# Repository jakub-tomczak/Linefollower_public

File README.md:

# Linefollower
Project created to compete with other linefollowers at PUT.

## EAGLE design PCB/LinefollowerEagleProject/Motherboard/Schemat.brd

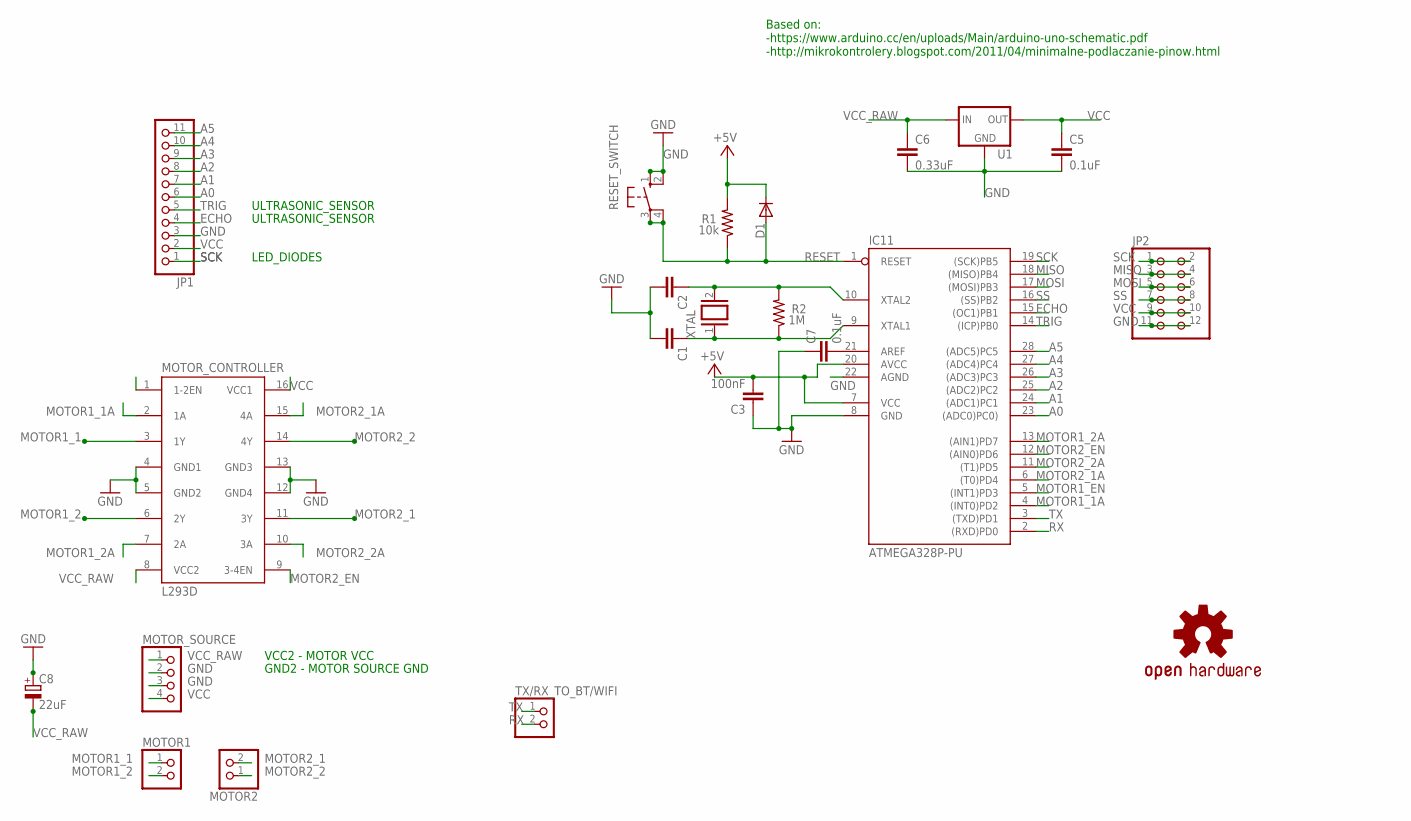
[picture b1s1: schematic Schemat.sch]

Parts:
C1, C2: C-EU025-030X050; C025-030X050
C3: 100nF; C025-030X050
C5: 0.1uF; CAP-PTH-SMALL-KIT
C6: 0.33uF; CAP-PTH-SMALL-KIT
C7: 0.1uF; C025-030X050
C8: 22uF; E2,5-6E
D1: 1N4004; DO41-10
IC11: ATMEGA328P-PU; DIL28-3
JP1: PINHD-1X11; 1X11
JP2: PINHD-2X6; 2X06
LOGO1: OSHW-LOGOS-COPPER; OSHW-LOGO-S_COPPER
MOTOR1, MOTOR2: PINHD-1X2/90; 1X02/90
MOTOR_CONTROLLER: L293D; DIL16
MOTOR_SOURCE: PINHD-1X4; 1X04
R1: 10k; AXIAL-0.3
R2: 1M; AXIAL-0.3
RESET_SWITCH: 10-XX; B3F-10XX
TX/RX_TO_BT/WIFI: PINHD-1X2/90; 1X02/90
U1: V_REG_78XX-TO-220; TO-220-ALT
XTAL: XTAL/S; QS

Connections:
A0: IC11.23 ((ADC0)PC0)), JP1.6
A1: IC11.24 ((ADC1)PC1), JP1.7
A2: IC11.25 ((ADC2)PC2), JP1.8
A3: IC11.26 ((ADC3)PC3), JP1.9
A4: IC11.27 ((ADC4)PC4), JP1.10
A5: IC11.28 ((ADC5)PC5), JP1.11
ECHO: IC11.15 ((OC1)PB1), JP1.4
GND: C1.2, C2.2, C3.1, C5.2, C6.2, C7.1, C8.+, IC11.8 (GND), IC11.22 (AGND), JP1.3, JP2.11, JP2.12, MOTOR_CONTROLLER.4 (GND1), MOTOR_CONTROLLER.5 (GND2), MOTOR_CONTROLLER.12 (GND4), MOTOR_CONTROLLER.13 (GND3), MOTOR_SOURCE.2, MOTOR_SOURCE.3, RESET_SWITCH.1 (S), RESET_SWITCH.2 (S1), U1.GND
MISO: IC11.18 ((MISO)PB4), JP2.3, JP2.4
MOSI: IC11.17 ((MOSI)PB3), JP2.5, JP2.6
MOTOR1_1: MOTOR1.1, MOTOR_CONTROLLER.3 (1Y)
MOTOR1_1A: IC11.4 ((INT0)PD2), MOTOR_CONTROLLER.2 (1A)
MOTOR1_2: MOTOR1.2, MOTOR_CONTROLLER.6 (2Y)
MOTOR1_2A: IC11.13 ((AIN1)PD7), MOTOR_CONTROLLER.7 (2A)
MOTOR1_EN: IC11.5 ((INT1)PD3), MOTOR_CONTROLLER.1 (1-2EN)
MOTOR2_1: MOTOR2.2, MOTOR_CONTROLLER.11 (3Y)
MOTOR2_1A: IC11.6 ((T0)PD4), MOTOR_CONTROLLER.15 (4A)
MOTOR2_2: MOTOR2.1, MOTOR_CONTROLLER.14 (4Y)
MOTOR2_2A: IC11.11 ((T1)PD5), MOTOR_CONTROLLER.10 (3A)
MOTOR2_EN: IC11.12 ((AIN0)PD6), MOTOR_CONTROLLER.9 (3-4EN)
unnamed: C2.1, IC11.10 (XTAL2), R2.P$2 (2), XTAL.2
unnamed: C1.1, IC11.9 (XTAL1), R2.P$1 (1), XTAL.1
unnamed: C7.2, IC11.21 (AREF)
RESET: D1.A, IC11.1 (RESET), R1.P$1 (1), RESET_SWITCH.3, RESET_SWITCH.4 (P1)
RX: IC11.2 ((RXD)PD0), TX/RX_TO_BT/WIFI.2
SCK: IC11.19 ((SCK)PB5), JP1.1, JP2.1, JP2.2
SS: IC11.16 ((SS)PB2), JP2.7, JP2.8
TRIG: IC11.14 ((ICP)PB0), JP1.5
TX: IC11.3 ((TXD)PD1), TX/RX_TO_BT/WIFI.1
VCC: C3.2, C5.1, D1.C, IC11.7 (VCC), IC11.20 (AVCC), JP1.2, JP2.9, JP2.10, MOTOR_CONTROLLER.16 (VCC1), MOTOR_SOURCE.4, R1.P$2 (2), U1.OUT
VCC_RAW: C6.1, C8.-, MOTOR_CONTROLLER.8 (VCC2), MOTOR_SOURCE.1, U1.IN

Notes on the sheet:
Based on: -https://www.arduino.cc/en/uploads/Main/arduino-uno-schematic.pdf -http://mikrokontrolery.blogspot.com/2011/04/minimalne-podlaczanie-pinow.html
VCC2 - MOTOR VCC
GND2 - MOTOR SOURCE GND
LED_DIODES
ULTRASONIC_SENSOR

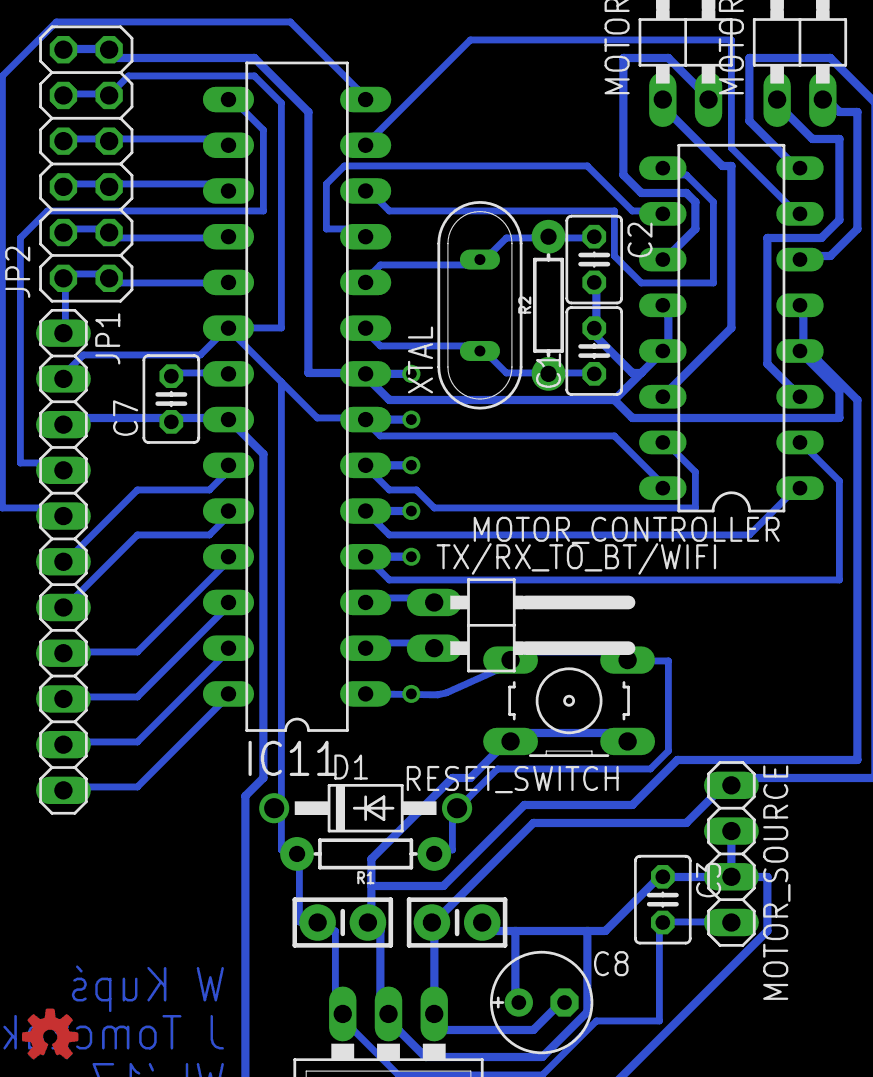
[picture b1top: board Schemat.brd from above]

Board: 2 copper layers, 22 parts (0 on the bottom side), 31 nets.

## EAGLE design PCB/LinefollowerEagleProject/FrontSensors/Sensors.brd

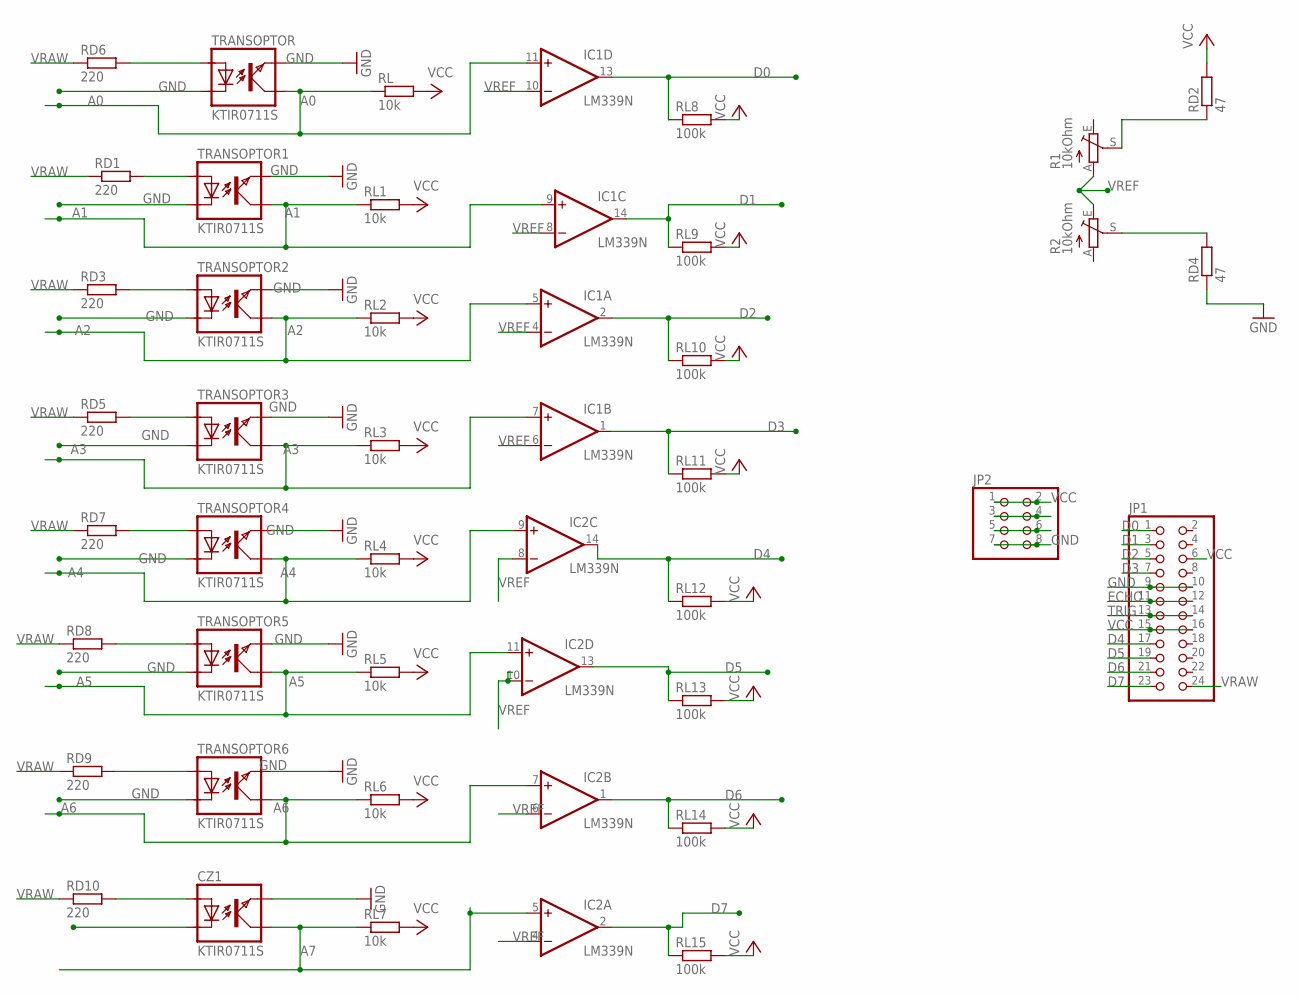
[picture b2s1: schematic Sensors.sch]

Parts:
CZ1: KTIR0711S; TOP
IC1, IC2: LM339N; DIL14
JP1: PINHD-2X12; 2X12
JP2: PINHD-2X4; 2X04
R1, R2: 10kOhm; CA6V
RD1, RD3, RD5, RD6, RD7, RD8, RD9, RD10: 220; 0204/7
RD2, RD4: 47; 0204/7
RL, RL1, RL2, RL3, RL4, RL5, RL6, RL7: 10k; 0204/7
RL8, RL9, RL10, RL11, RL12, RL13, RL14, RL15: 100k; 0204/7
TRANSOPTOR, TRANSOPTOR1, TRANSOPTOR2, TRANSOPTOR3, TRANSOPTOR4, TRANSOPTOR5, TRANSOPTOR6: KTIR0711S; TOP

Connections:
A0: IC1.11 (+IN), RL.1, TRANSOPTOR.KOLEKTOR
A1: IC1.9 (+IN), RL1.1, TRANSOPTOR1.KOLEKTOR
A2: IC1.5 (+IN), RL2.1, TRANSOPTOR2.KOLEKTOR
A3: IC1.7 (+IN), RL3.1, TRANSOPTOR3.KOLEKTOR
A4: IC2.9 (+IN), RL4.1, TRANSOPTOR4.KOLEKTOR
A5: IC2.11 (+IN), RL5.1, TRANSOPTOR5.KOLEKTOR
A6: IC2.7 (+IN), RL6.1, TRANSOPTOR6.KOLEKTOR
A7: CZ1.KOLEKTOR, IC2.5 (+IN), RL7.1
D0: IC1.13 (OUT), JP1.1, RL8.1
D1: IC1.14 (OUT), JP1.3, RL9.1
D2: IC1.2 (OUT), JP1.5, RL10.1
D3: IC1.1 (OUT), JP1.7, RL11.1
D4: IC2.14 (OUT), JP1.17, RL12.1
D5: IC2.13 (OUT), JP1.19, RL13.1
D6: IC2.1 (OUT), JP1.21, RL14.1
D7: IC2.2 (OUT), JP1.23, RL15.1
DIODE0: RD6.2, TRANSOPTOR.ANODA
DIODE1: RD3.2, TRANSOPTOR2.ANODA
DIODE2: RD1.2, TRANSOPTOR1.ANODA
DIODE3: RD5.2, TRANSOPTOR3.ANODA
DIODE4: RD7.2, TRANSOPTOR4.ANODA
DIODE5: RD8.2, TRANSOPTOR5.ANODA
DIODE6: RD9.2, TRANSOPTOR6.ANODA
DIODE7: CZ1.ANODA, RD10.2
ECHO: JP1.11, JP1.12, JP2.5, JP2.6
GND: CZ1.EMITER, CZ1.KATODA, IC1.12 (GND), IC2.12 (GND), JP1.9, JP1.10, JP2.7, JP2.8, RD4.1, TRANSOPTOR.EMITER, TRANSOPTOR.KATODA, TRANSOPTOR1.EMITER, TRANSOPTOR1.KATODA, TRANSOPTOR2.EMITER, TRANSOPTOR2.KATODA, TRANSOPTOR3.EMITER, TRANSOPTOR3.KATODA, TRANSOPTOR4.EMITER, TRANSOPTOR4.KATODA, TRANSOPTOR5.EMITER, TRANSOPTOR5.KATODA, TRANSOPTOR6.EMITER, TRANSOPTOR6.KATODA
unnamed: R2.S, RD4.2
unnamed: R1.S, RD2.1
TRIG: JP1.13, JP1.14, JP2.3, JP2.4
VCC: IC1.3 (V+), IC2.3 (V+), JP1.6, JP1.15, JP1.16, JP2.1, JP2.2, RD2.2, RL.2, RL1.2, RL2.2, RL3.2, RL4.2, RL5.2, RL6.2, RL7.2, RL8.2, RL9.2, RL10.2, RL11.2, RL12.2, RL13.2, RL14.2, RL15.2
VRAW: JP1.24, RD1.1, RD3.1, RD5.1, RD6.1, RD7.1, RD8.1, RD9.1, RD10.1
VREF: IC1.4 (-IN), IC1.6 (-IN), IC1.8 (-IN), IC1.10 (-IN), IC2.4 (-IN), IC2.6 (-IN), IC2.8 (-IN), IC2.10 (-IN), R1.A, R2.E

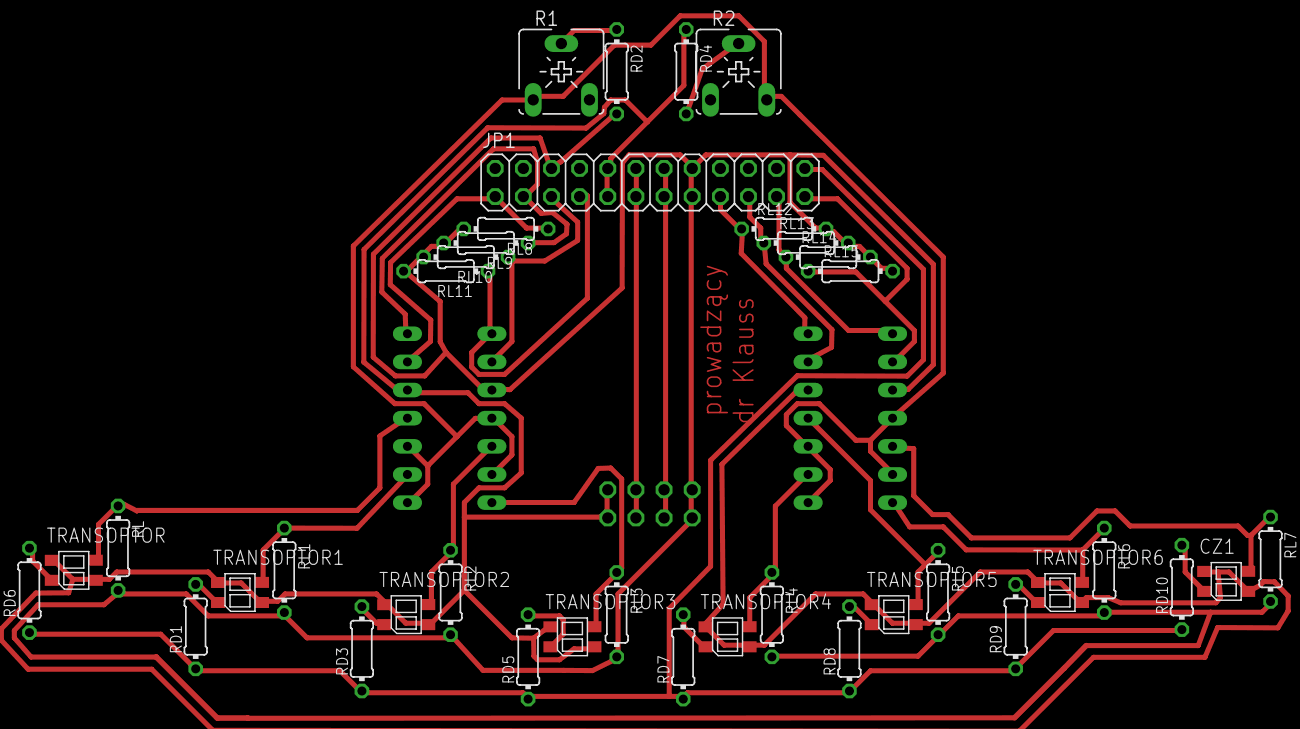
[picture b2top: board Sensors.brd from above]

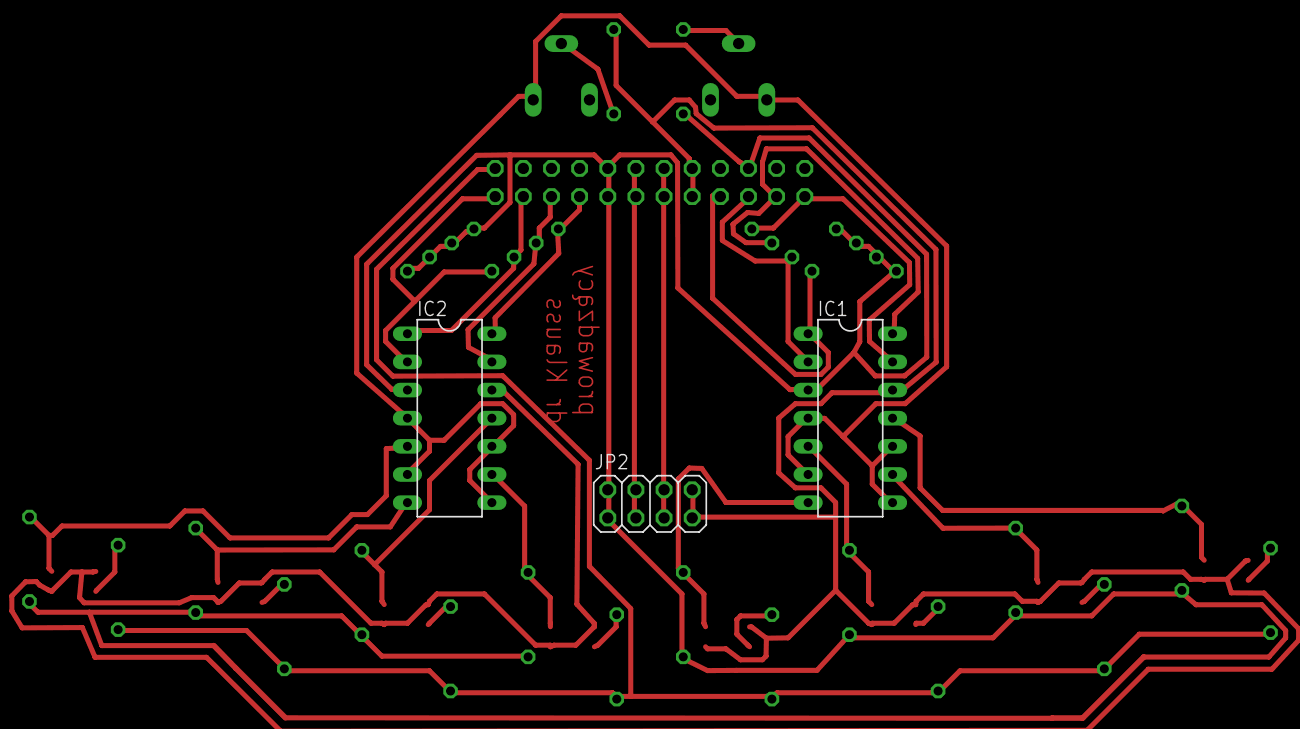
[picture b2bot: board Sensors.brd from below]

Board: 2 copper layers, 40 parts (3 on the bottom side), 32 nets.

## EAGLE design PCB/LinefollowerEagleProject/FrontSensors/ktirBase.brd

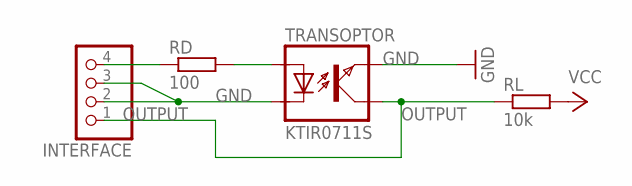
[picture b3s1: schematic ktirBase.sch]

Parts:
INTERFACE: PINHD-1X4/90; 1X04/90
RD: 100; 0204/7
RL: 10k; 0204/7
TRANSOPTOR: KTIR0711S; TOP

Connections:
ANODE: RD.2, TRANSOPTOR.ANODA
GND: INTERFACE.2, INTERFACE.3, TRANSOPTOR.EMITER, TRANSOPTOR.KATODA
OUTPUT: INTERFACE.1, RL.1, TRANSOPTOR.KOLEKTOR
VCC: INTERFACE.4, RD.1, RL.2

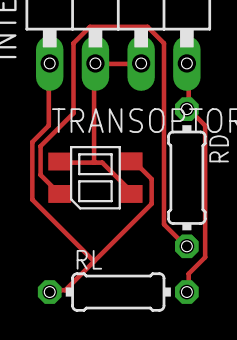
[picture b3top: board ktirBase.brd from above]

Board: 2 copper layers, 4 parts (0 on the bottom side), 4 nets.

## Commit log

2017-05-30 First commit - migration from private repo.
2017-05-30 Update .gitignore
    Exclude *.vcxproj.user.
2017-06-01 Update project

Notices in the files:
parts and their libraries:
SparkFun-Resistors: Licensing: Creative Commons ShareAlike 4.0 International - https://creativecommons.org/licenses/by-sa/4.0
